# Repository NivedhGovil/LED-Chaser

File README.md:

## LED Chaser

This project is an **LED Chaser**: a series of 10 LEDs that light up in a sequence. 

## In this repository
Bill Of Materials.csv : Bill of Materials, all parts required and their descriptions.  <br> 
Journal.md: A journal on my progress with making this project. <br> 
schematic.png: A screenshot of the Schematic <br> 
PCB_PCB_LED-Chaser-New_2026-10-12.json: The EasyEDA export of the PCB in json <br> 
PCB_PCB_LED-Chaser-New_2026-10-12.kicad_pcb: The PCB file of kicad. <br> 
SCH_LED-Chaser-New_2026-10-12.json: The EasyEDA export of the schematic in json.<br> 

*No firmware needed.*

<br>

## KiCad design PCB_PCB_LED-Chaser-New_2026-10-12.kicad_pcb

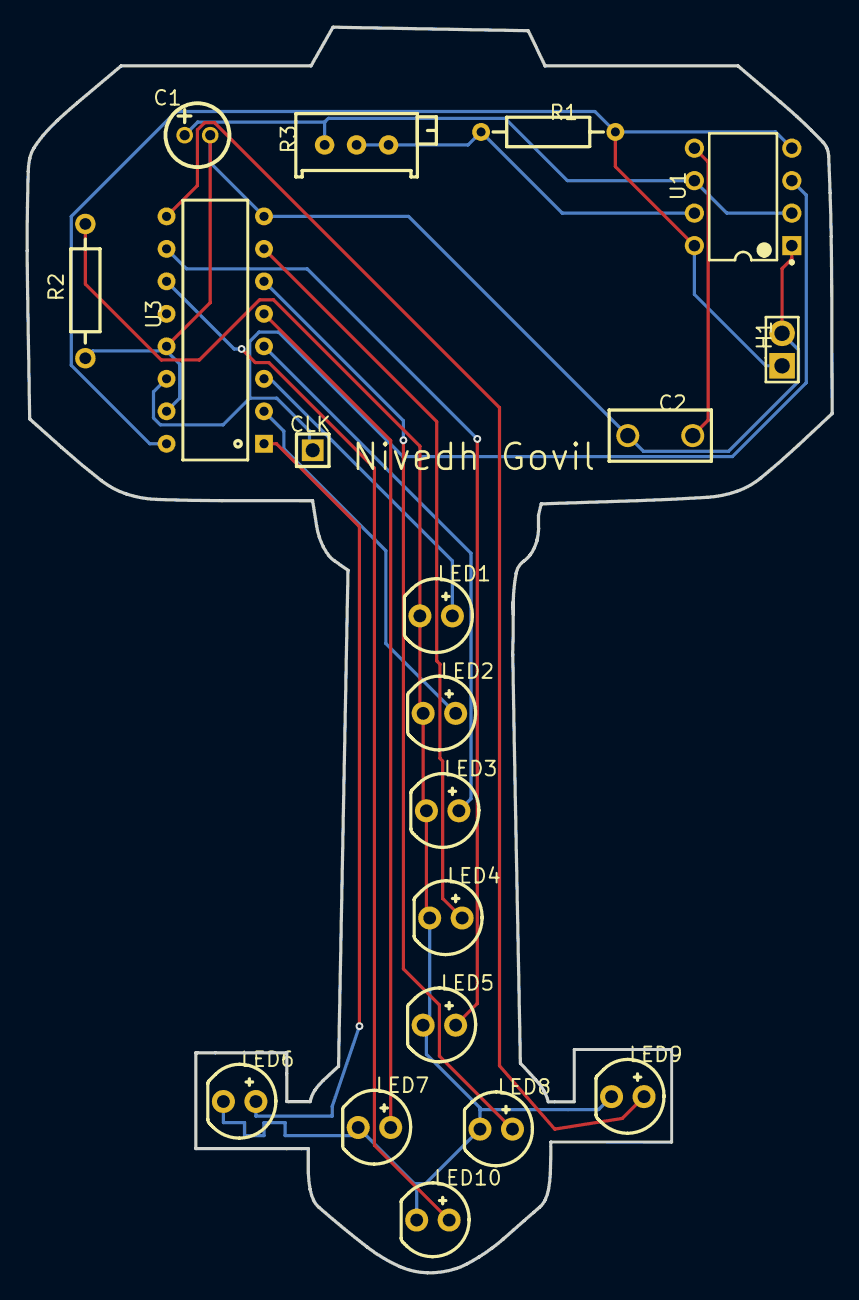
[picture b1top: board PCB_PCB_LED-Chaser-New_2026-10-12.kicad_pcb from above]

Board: 2 copper layers, 62.9 x 97.4 mm, 19 parts (0 on the bottom side), 17 nets.

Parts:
C1: 10uF; CAP-TH_BD5.0-P2.00-D0.8-FD
C2: 0.01u; CAP-TH_L8.0-W4.0-P5.00-D1.2
CLK: Header-Male-2.54_1x1; HDR-TH_1P-P2.54-V-M
H1: PZ254V-11-02P; HDR-TH_2P-P2.54-V-M
LED1, LED2, LED3, LED4, LED5, LED6, LED7, LED8, LED9, LED10: XL-502UWC; LED-TH_BD5.9-P2.54-RD_WHITE
R1: 1kΩ; RES-TH_BD2.3-L6.5-P10.50-D0.5
R2: 470Ω; RES-TH_BD2.2-L6.5-P10.50-D0.6
R3: 50kΩ; RES-ADJ-TH_3P-L9.5-W4.85-P2.50-BL-L
U1: 100 Hz; DIP-8_L9.8-W6.6-P2.54-LS7.6-BL
U3: CD4017BCN; DIP16

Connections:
LED1_2: LED1.2, U3.3
LED2_2: LED2.2, U3.2
LED3_2: LED3.2, U3.4
LED4_2: LED4.2, U3.7
LED5_2: LED5.2, U3.10
LED6_2: LED6.2, U3.1
LED7_2: LED7.2, U3.5
LED8_2: LED8.2, U3.6
LED9_2: LED9.2, U3.9
LED10_2: LED10.2, U3.11
R2_2: LED1.1, LED2.1, LED3.1, LED4.1, LED5.1, LED6.1, LED7.1, LED8.1, LED9.1, LED10.1, R2.2
U1_1: C1.2, C2.1, H1.2, R2.1, U1.1, U3.8, U3.13, U3.15
U1_2: C1.1, R3.1, U1.2, U1.6
U1_3: CLK.1, U1.3, U3.14
U1_4: H1.1, R1.2, U1.4, U1.8, U3.16
U1_5: C2.2, U1.5
U1_7: R1.1, R3.2, R3.3, U1.7

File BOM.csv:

Part Name,Qty,Price  (USD),Item link,Notes
"NE555P timer IC, DIP-8 (U1)",1,1.33,https://www.lcsc.com/product-detail/C46749.html,"TI NE555P, LCSC C46749. Min order 5 @ $0.2667."
"CD4017 decade counter, DIP-16 (U3)",1,0.18,https://www.lcsc.com/product-detail/C51939979.html,"Design specifies CD4017BCN, which has no LCSC part. TI CD4017BE (C34519) is currently not available, so this uses the pin-compatible CD4017DA16.TB (C51939979) at $0.1791. Check its minimum order before buying."
"White LED, 5mm through-hole (LED1-LED10)",10,0.54,https://www.lcsc.com/product-detail/C2895480.html,"XINGLIGHT XL-502UWC, LCSC C2895480. Min order 20 @ $0.0271."
"Resistor 1k, 1/4W metal film (R1)",1,0.53,https://www.lcsc.com/product-detail/C713997.html,"MF1/4W-1K 1%, LCSC C713997. Min order 50 @ $0.0105."
"Resistor 470 ohm, 1/4W metal film (R2)",1,0.59,https://www.lcsc.com/product-detail/C58592.html,"UNI-ROYAL MFR0W4F4700A50, LCSC C58592. Min order 50 @ $0.0117."
"Trimmer pot 50k, 3296X multi-turn (R3)",1,0.97,https://www.lcsc.com/product-detail/C118912.html,"BOCHEN 3296X-1-503, LCSC C118912. Min order 5 @ $0.1947. Only 95 in stock; 3296W-1-503 (C118911) is the same part with the screw on top."
"Electrolytic capacitor 1uF 50V, 5mm (C1)",1,0.54,https://www.lcsc.com/product-detail/C62934.html,"CapXon KF010M050C110A, LCSC C62934. OUT OF STOCK; price is LCSC's reference for 20 pcs. Any 1uF 16V+ radial electrolytic with 2mm lead spacing will fit."
"Ceramic capacitor 10nF (0.01uF), 5mm pitch (C2)",1,0.8,https://www.lcsc.com/product-detail/C249157.html,"STE N09F1B103MN0B0S0N0, LCSC C249157. Min order 20 @ $0.0402."
"Pin header 1x2, 2.54mm (H1, VCC/GND)",1,0.9,https://www.lcsc.com/product-detail/C492401.html,"XFCN PZ254V-11-02P, LCSC C492401. Min order 50 @ $0.0179."
"Pin header 1x1, 2.54mm (CLK test point)",1,0.64,https://www.lcsc.com/product-detail/C81276.html,"BOOMELE 2.54-1*1P, LCSC C81276. Min order 50 @ $0.0128."
,,,,
Total Price (USD):,,7.02,,"Prices are LCSC USD on 5 Oct 2026 at minimum order quantity, excluding shipping, taxes, and the PCB itself."
